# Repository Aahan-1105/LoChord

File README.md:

# LoChord
I wanted to create a cool synth keypad for music week in the Half-Life Challenge by Hack Club. Given my lack of experience in the realm, I chose to follow along with the MIDI Keypad tutorial by Kai. My project is inspired by the HiChord and aptly named the LoChord.

I wanted to get an ENIG surface for this PCB but unfortunately that was well outside of the budget and would cost an extra $18 USD.

## Goals and Features
- 7 Capacitive Touch Inputs
- 6 Modifier Keys based on the KailH Choc V1 Switch (Hot-swappable)
- A Rotary Encoder for easy volume control
- Swappable ESP32-S3-ZERO
- DIY Cost Under $40 USD!

## Photos and Render

Schematic

PCB Layout and Traces

PCB Render in KiCad 3D Viewer

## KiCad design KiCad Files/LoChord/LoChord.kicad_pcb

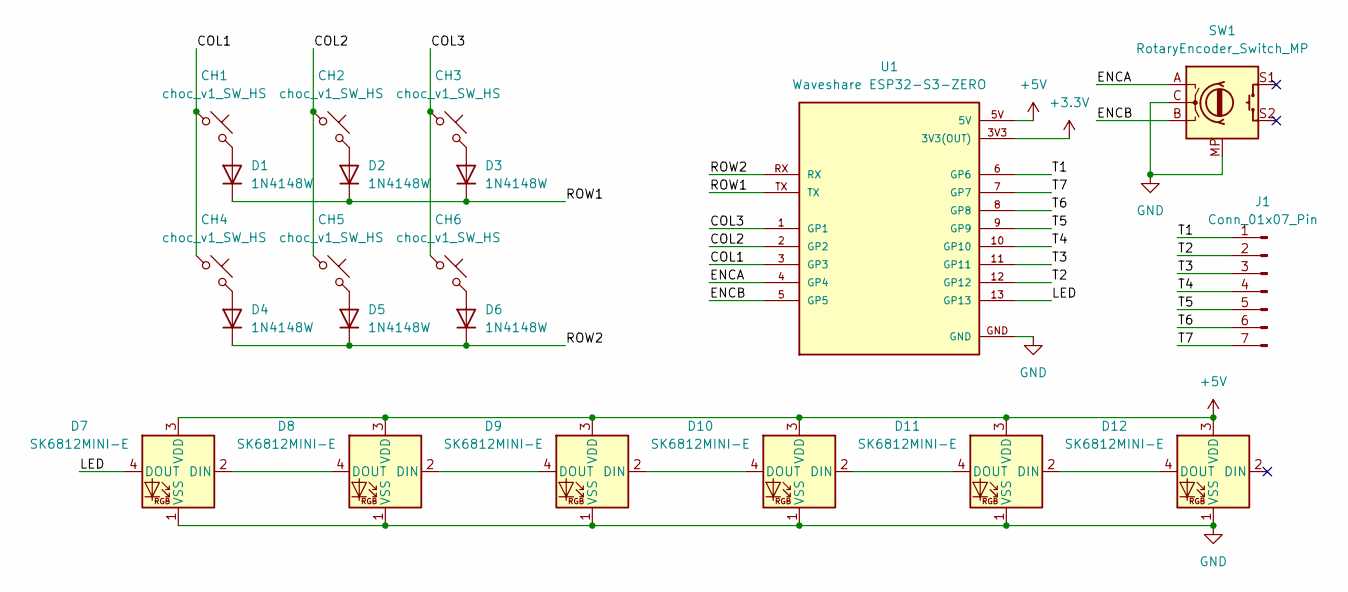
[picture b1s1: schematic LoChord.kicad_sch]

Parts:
CH1, CH2, CH3, CH4, CH5, CH6: choc_v1_SW_HS; SW_choc_v1_HS_CPG135001S30_1u
D1, D2, D3, D4, D5, D6: 1N4148W; D_SOD-123
D7, D8, D9, D10, D11, D12: SK6812MINI-E; LED_SK6812MINI-E_3.2x2.8mm_P1.5mm_ReverseMount
J1: Conn_01x07_Pin; Capacitive Keys
SW1: RotaryEncoder_Switch_MP; RotaryEncoder_Alps_EC11E-Switch_Vertical_H20mm
U1: Waveshare ESP32-S3-ZERO; Waveshare ESP32-S3-Zero; PARTREV NA

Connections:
+3.3V: U1.3V3 (3V3(OUT))
+5V: D7.3 (VDD), D8.3 (VDD), D9.3 (VDD), D10.3 (VDD), D11.3 (VDD), D12.3 (VDD), U1.5V
/COL1: CH1.1, CH4.1, U1.3 (GP3)
/COL2: CH2.1, CH5.1, U1.2 (GP2)
/COL3: CH3.1, CH6.1, U1.1 (GP1)
/ENCA: SW1.A, U1.4 (GP4)
/ENCB: SW1.B, U1.5 (GP5)
/LED: D7.4 (DOUT), U1.13 (GP13)
/ROW1: D1.1 (K), D2.1 (K), D3.1 (K), U1.TX
/ROW2: D4.1 (K), D5.1 (K), D6.1 (K), U1.RX
/T1: J1.1, U1.6 (GP6)
/T2: J1.2, U1.12 (GP12)
/T3: J1.3, U1.11 (GP11)
/T4: J1.4, U1.10 (GP10)
/T5: J1.5, U1.9 (GP9)
/T6: J1.6, U1.8 (GP8)
/T7: J1.7, U1.7 (GP7)
GND: D7.1 (VSS), D8.1 (VSS), D9.1 (VSS), D10.1 (VSS), D11.1 (VSS), D12.1 (VSS), SW1.C, SW1.MP, U1.GND
unnamed: CH1.2, D1.2 (A)
unnamed: CH2.2, D2.2 (A)
unnamed: CH3.2, D3.2 (A)
unnamed: CH4.2, D4.2 (A)
unnamed: CH5.2, D5.2 (A)
unnamed: CH6.2, D6.2 (A)
unnamed: D7.2 (DIN), D8.4 (DOUT)
unnamed: D8.2 (DIN), D9.4 (DOUT)
unnamed: D10.2 (DIN), D11.4 (DOUT)
unnamed: D9.2 (DIN), D10.4 (DOUT)
unnamed: D11.2 (DIN), D12.4 (DOUT)

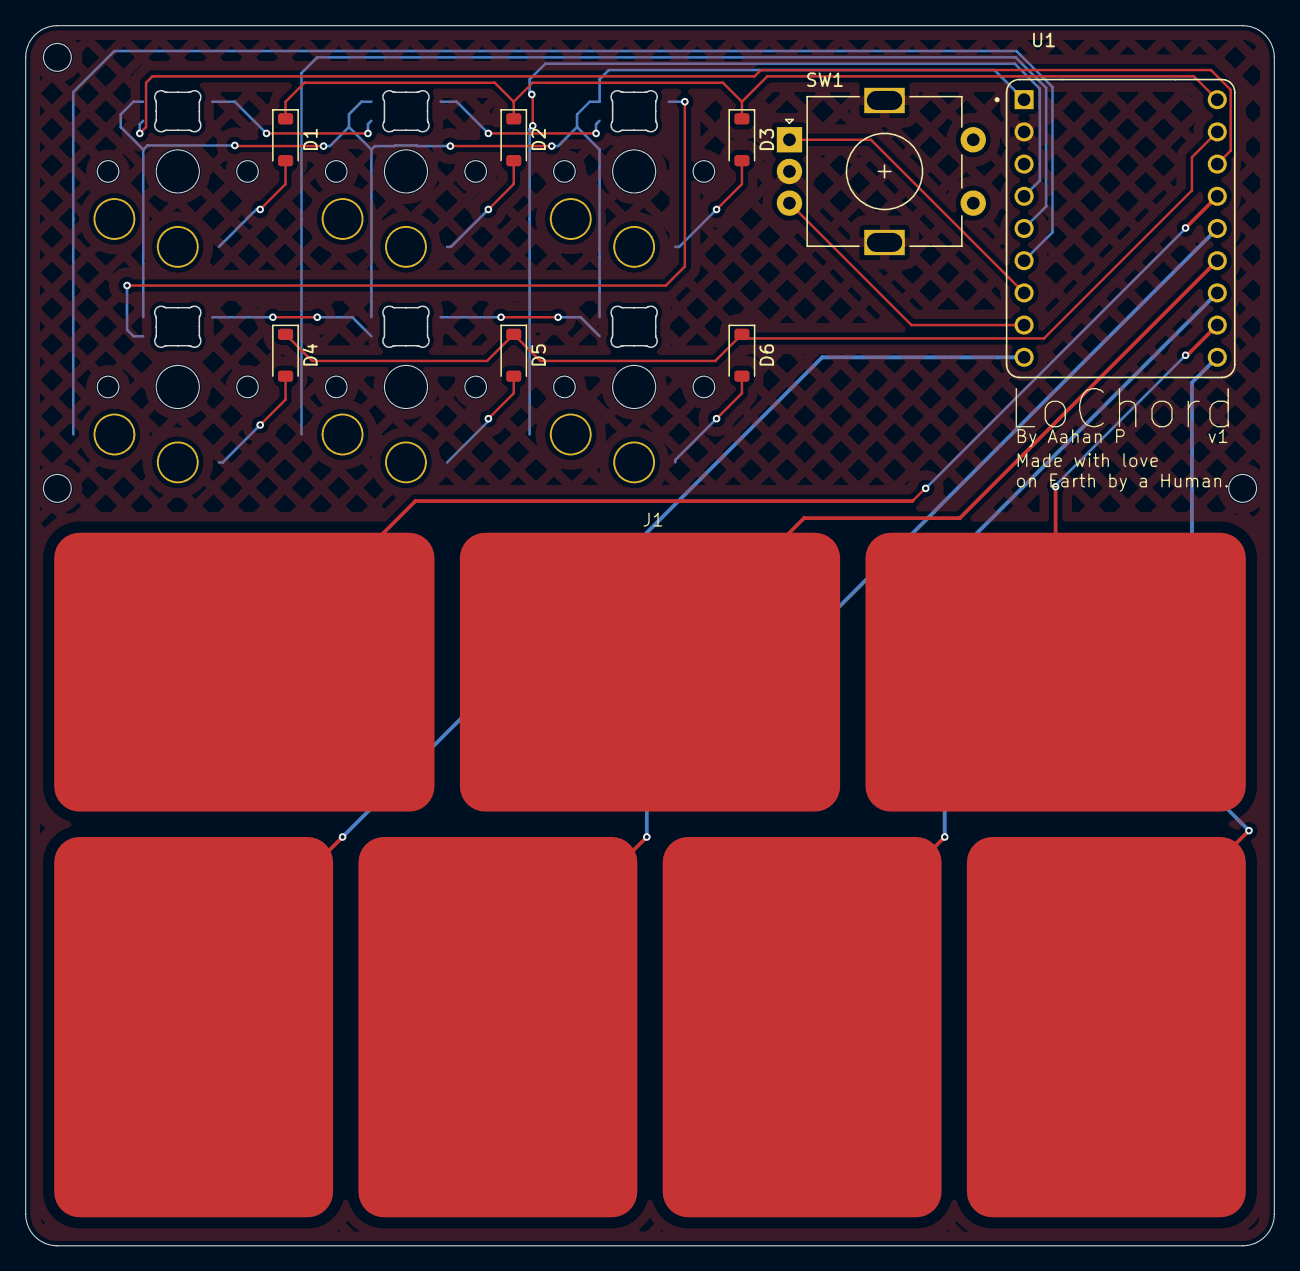
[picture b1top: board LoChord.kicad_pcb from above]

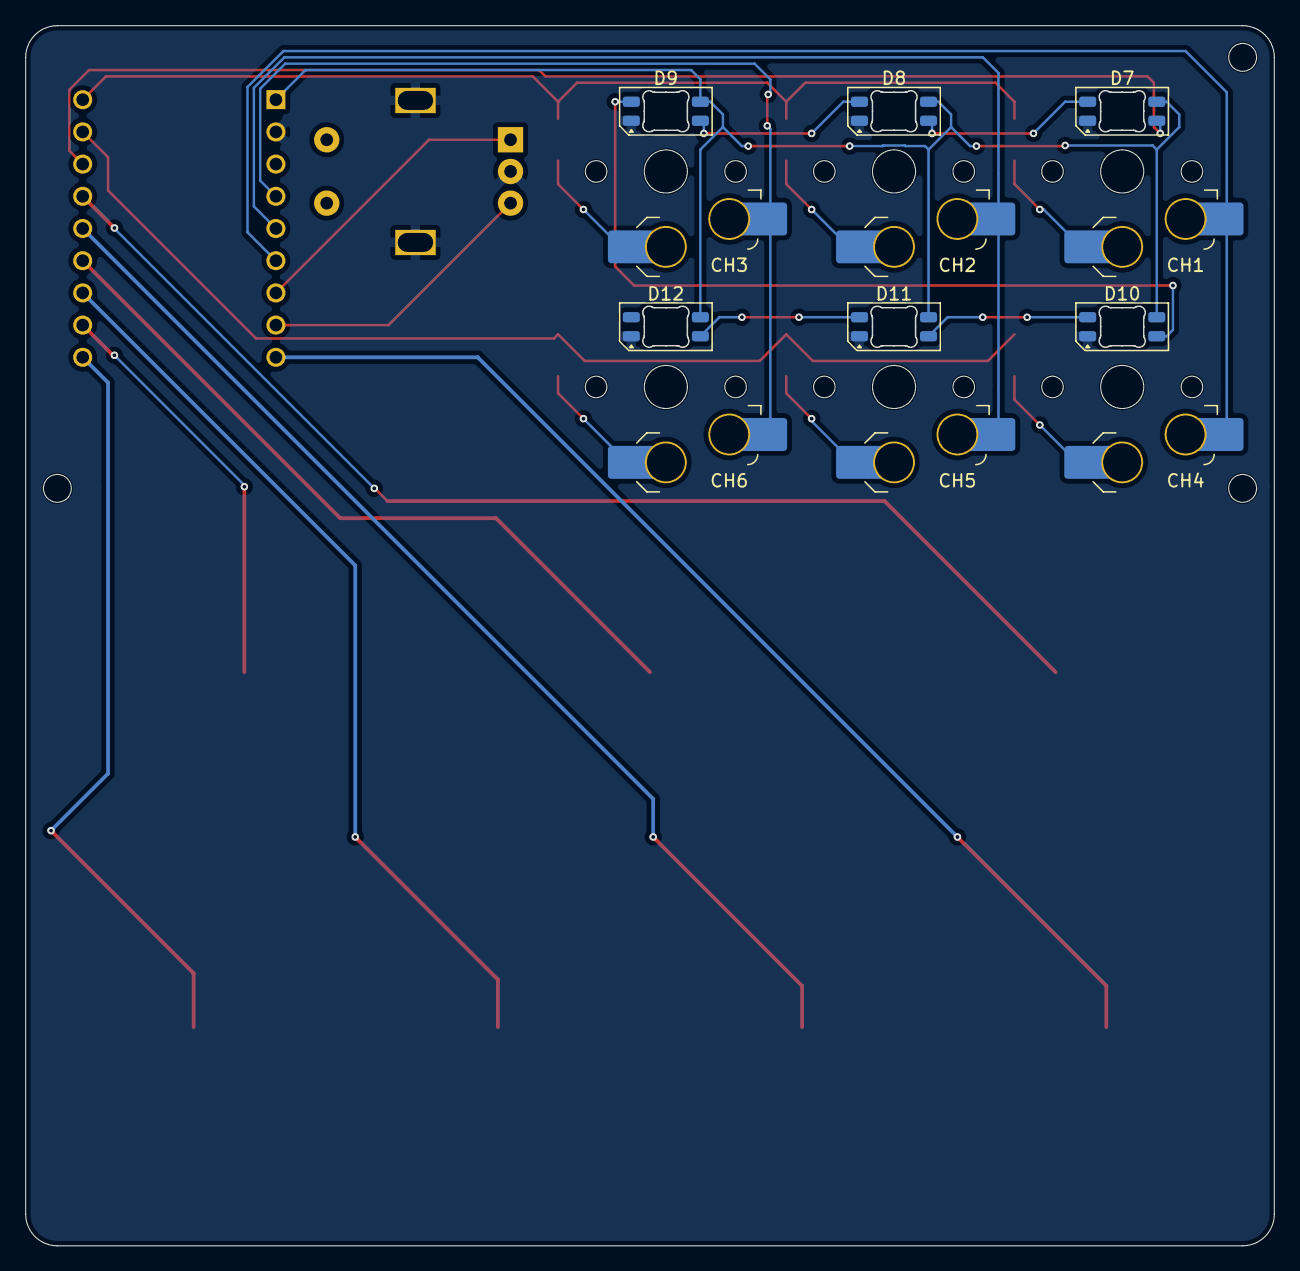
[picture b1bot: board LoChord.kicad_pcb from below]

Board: 2 copper layers, 98.5 x 96.2 mm, 21 parts (12 on the bottom side), 28 nets.

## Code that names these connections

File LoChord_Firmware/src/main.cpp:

/**
 * @file main.cpp
 * @brief LoChord - Standalone USB-MIDI & Chord Controller Firmware
 * Target: Waveshare ESP32-S3-Zero / Clone
 */

#include <Arduino.h>
#include <Adafruit_NeoPixel.h>
#include <FS.h>
#include "USB.h"
#include "USBMIDI.h"

USBMIDI MIDI;

// -------------------------------------------------------------
// Pin Definitions (Matched to your Schematic)
// -------------------------------------------------------------
#define LED_PIN       13
#define NUM_LEDS      6

#define ENCODER_A     4
#define ENCODER_B     5

const uint8_t ROW_PINS[2] = {44, 43}; // ROW1 (RX/GPIO44), ROW2 (TX/GPIO43)
const uint8_t COL_PINS[3] = {1, 2, 3};   // COL1 (GP1), COL2 (GP2), COL3 (GP3)

// 7 Touch Pads mapped to GP6 through GP12
const uint8_t TOUCH_PINS[7] = {6, 7, 8, 9, 10, 11, 12}; 
const int TOUCH_THRESHOLD = 30000; 

// -------------------------------------------------------------
// Global States & Mappings
// -------------------------------------------------------------
Adafruit_NeoPixel leds(NUM_LEDS, LED_PIN, NEO_GRB + NEO_KHZ800);

bool matrixState[2][3] = {{false, false, false}, {false, false, false}};
bool touchState[7] = {false, false, false, false, false, false, false};

int lastEncoderA = HIGH;
uint8_t masterVolume = 100; // Default volume (0-127)

// Base diatonic notes for touch pads (C4 major scale)
const uint8_t TOUCH_MIDI_NOTES[7] = {60, 62, 64, 65, 67, 69, 71}; 

// Active octave transpose offset controlled by modifiers
int octaveOffset = 0; 

// -------------------------------------------------------------
// Function Prototypes
// -------------------------------------------------------------
void scanTouchPads();
void scanModifiers();
void scanEncoder();

// -------------------------------------------------------------
// Setup
// -------------------------------------------------------------
void setup() {
  Serial.begin(115200);

  MIDI.begin();
  USB.begin();

  leds.begin();
  leds.setBrightness(35);
  leds.clear();
  leds.show();

  pinMode(ENCODER_A, INPUT_PULLUP);
  pinMode(ENCODER_B, INPUT_PULLUP);
  lastEncoderA = digitalRead(ENCODER_A);

  for (int r = 0; r < 2; r++) {
    pinMode(ROW_PINS[r], OUTPUT);
    digitalWrite(ROW_PINS[r], HIGH);
  }
  for (int c = 0; c < 3; c++) {
    pinMode(COL_PINS[c], INPUT_PULLUP);
  }
}

// -------------------------------------------------------------
// Main Loop
// -------------------------------------------------------------
void loop() {
  scanTouchPads();
  scanModifiers();
  scanEncoder();
  
  delay(4);
}

// -------------------------------------------------------------
// Input Scanners
// -------------------------------------------------------------

void scanTouchPads() {
  for (int i = 0; i < 7; i++) {
    int touchVal = touchRead(TOUCH_PINS[i]);
    bool pressed = (touchVal > TOUCH_THRESHOLD);

    uint8_t finalNote = TOUCH_MIDI_NOTES[i] + (octaveOffset * 12);

    if (pressed && !touchState[i]) {
      touchState[i] = true;
      MIDI.noteOn(0, finalNote, 127);
      
      if (i < NUM_LEDS) {
        leds.setPixelColor(i, leds.Color(0, 200, 255));
        leds.show();
      }
    } else if (!pressed && touchState[i]) {
      touchState[i] = false;
      MIDI.noteOff(0, finalNote, 0);
      
      if (i < NUM_LEDS) {
        leds.setPixelColor(i, leds.Color(0, 0, 0));
        leds.show();
      }
    }
  }
}

void scanModifiers() {
  for (int r = 0; r < 2; r++) {
    digitalWrite(ROW_PINS[r], LOW);
    
    for (int c = 0; c < 3; c++) {
      bool pressed = (digitalRead(COL_PINS[c]) == LOW);
      
      if (pressed && !matrixState[r][c]) {
        matrixState[r][c] = true;

        if (r == 0 && c == 0) {
          octaveOffset = -1; 
        } else if (r == 0 && c == 1) {
          octaveOffset = 0;  
        } else if (r == 0 && c == 2) {
          octaveOffset = 1;  
        }
        
      } else if (!pressed && matrixState[r][c]) {
        matrixState[r][c] = false;
      }
    }
    digitalWrite(ROW_PINS[r], HIGH);
  }
}

void scanEncoder() {
  int currentA = digitalRead(ENCODER_A);
  
  if (currentA != lastEncoderA && currentA == LOW) {
    if (digitalRead(ENCODER_B) != currentA) {
      if (masterVolume < 127) masterVolume += 4;
      if (masterVolume > 127) masterVolume = 127;
    } else {
      if (masterVolume > 4) masterVolume -= 4;
      else masterVolume = 0;
    }
    MIDI.controlChange(0, 7, masterVolume);
  }
  lastEncoderA = currentA;
}
